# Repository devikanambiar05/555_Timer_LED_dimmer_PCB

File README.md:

# 555 Timer LED Dimmer Circuit

This project contains the KiCad project files for a custom-designed PCB of a 555 Timer-based LED dimmer circuit. The circuit uses the NE555 timer IC to generate a PWM (Pulse Width Modulation) signal, allowing the brightness of an LED to be controlled by adjusting the duty cycle.

## Circuit Design

The circuit is based on the NE555 timer IC configured in astable mode to generate a PWM signal. The duty cycle of the output signal can be varied using a potentiometer, which controls the brightness of the connected LED.

The 555 timer continuously generates pulses at a fixed frequency, while adjusting the potentiometer changes the ON and OFF time of the output signal. This allows smooth LED brightness control without significantly changing the LED's operating voltage.

The circuit is powered using a DC supply, and the output stage controls the LED according to the generated PWM signal.

Below is the schematic of the LED dimmer circuit.

## PCB Design

The PCB layout for the circuit is designed using KiCad. The components are arranged to keep the circuit compact and ensure proper routing between the 555 timer, timing components, potentiometer, and LED output stage.

The PCB includes footprints for all the required components, along with input power and output connections. The potentiometer is accessible for convenient adjustment of LED brightness.

Below is the final PCB layout after routing.

## 3D View

The 3D view of the finalized PCB provides a representation of the assembled board, showing the component placement and overall PCB dimensions.

## Technologies Used

- KiCad
- NE555 Timer IC
- PWM (Pulse Width Modulation)
- PCB Design and Routing

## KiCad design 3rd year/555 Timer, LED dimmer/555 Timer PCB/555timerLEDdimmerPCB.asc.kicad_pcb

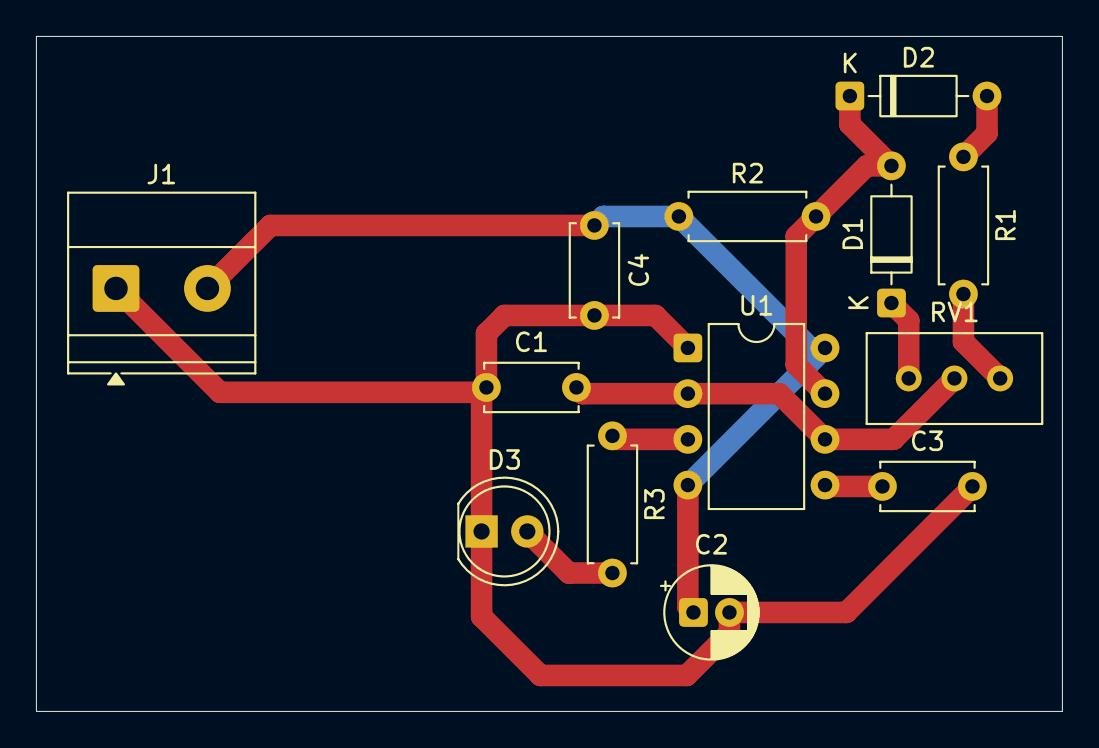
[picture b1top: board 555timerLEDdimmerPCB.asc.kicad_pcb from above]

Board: 2 copper layers, 57.0 x 37.5 mm, 13 parts (0 on the bottom side), 10 nets.

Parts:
C1: 1n; C_Disc_D5.0mm_W2.5mm_P5.00mm
C2: 10u; CP_Radial_D5.0mm_P2.00mm
C3, C4: 10n; C_Disc_D5.0mm_W2.5mm_P5.00mm
D1, D2: D; D_DO-35_SOD27_P7.62mm_Horizontal
D3: LED; LED_D5.0mm
J1: Screw_Terminal_01x02; TerminalBlock_Phoenix_MKDS-1,5-2-5.08_1x02_P5.08mm_Horizont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
R1: 100; R_Axial_DIN0207_L6.3mm_D2.5mm_P7.62mm_Horizontal
R2: 2.2k; R_Axial_DIN0207_L6.3mm_D2.5mm_P7.62mm_Horizontal
R3: 470; R_Axial_DIN0207_L6.3mm_D2.5mm_P7.62mm_Horizontal
RV1: R_Potentiometer; Potentiometer_Bourns_3296W_Vertical
U1: NE555P; DIP-8_W7.62mm

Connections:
unnamed: D1.2 (A), D2.1 (K), R2.2, U1.7 (DISCH)
unnamed: D1.1 (K), RV1.3
unnamed: D2.2 (A), R1.1
unnamed: D3.2 (A), R3.2
unnamed: C1.1, C2.2, C3.2, C4.2, D3.1 (K), J1.1, U1.1 (GND)
unnamed: C2.1, C4.1, J1.2, R2.1, U1.4 (~RST), U1.8 (VCC)
unnamed: R1.2, RV1.1
unnamed: C3.1, U1.5 (CONT)
unnamed: R3.1, U1.3 (OUT)
unnamed: C1.2, RV1.2, U1.2 (TRIG), U1.6 (THRES)
